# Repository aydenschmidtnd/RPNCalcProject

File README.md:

# RPNCalcProject

Due to the cost of reverse polish notation (RPN) calculators, I wanted to make the attempt at creating one myself.
I would do this all from scratch making my own PCB, creating my own code, and figuring out how to create a calculator-like case.

I want to go ahead and do this with the MSP430G2533 Microcontroller since I have a development board with me with that MCU.

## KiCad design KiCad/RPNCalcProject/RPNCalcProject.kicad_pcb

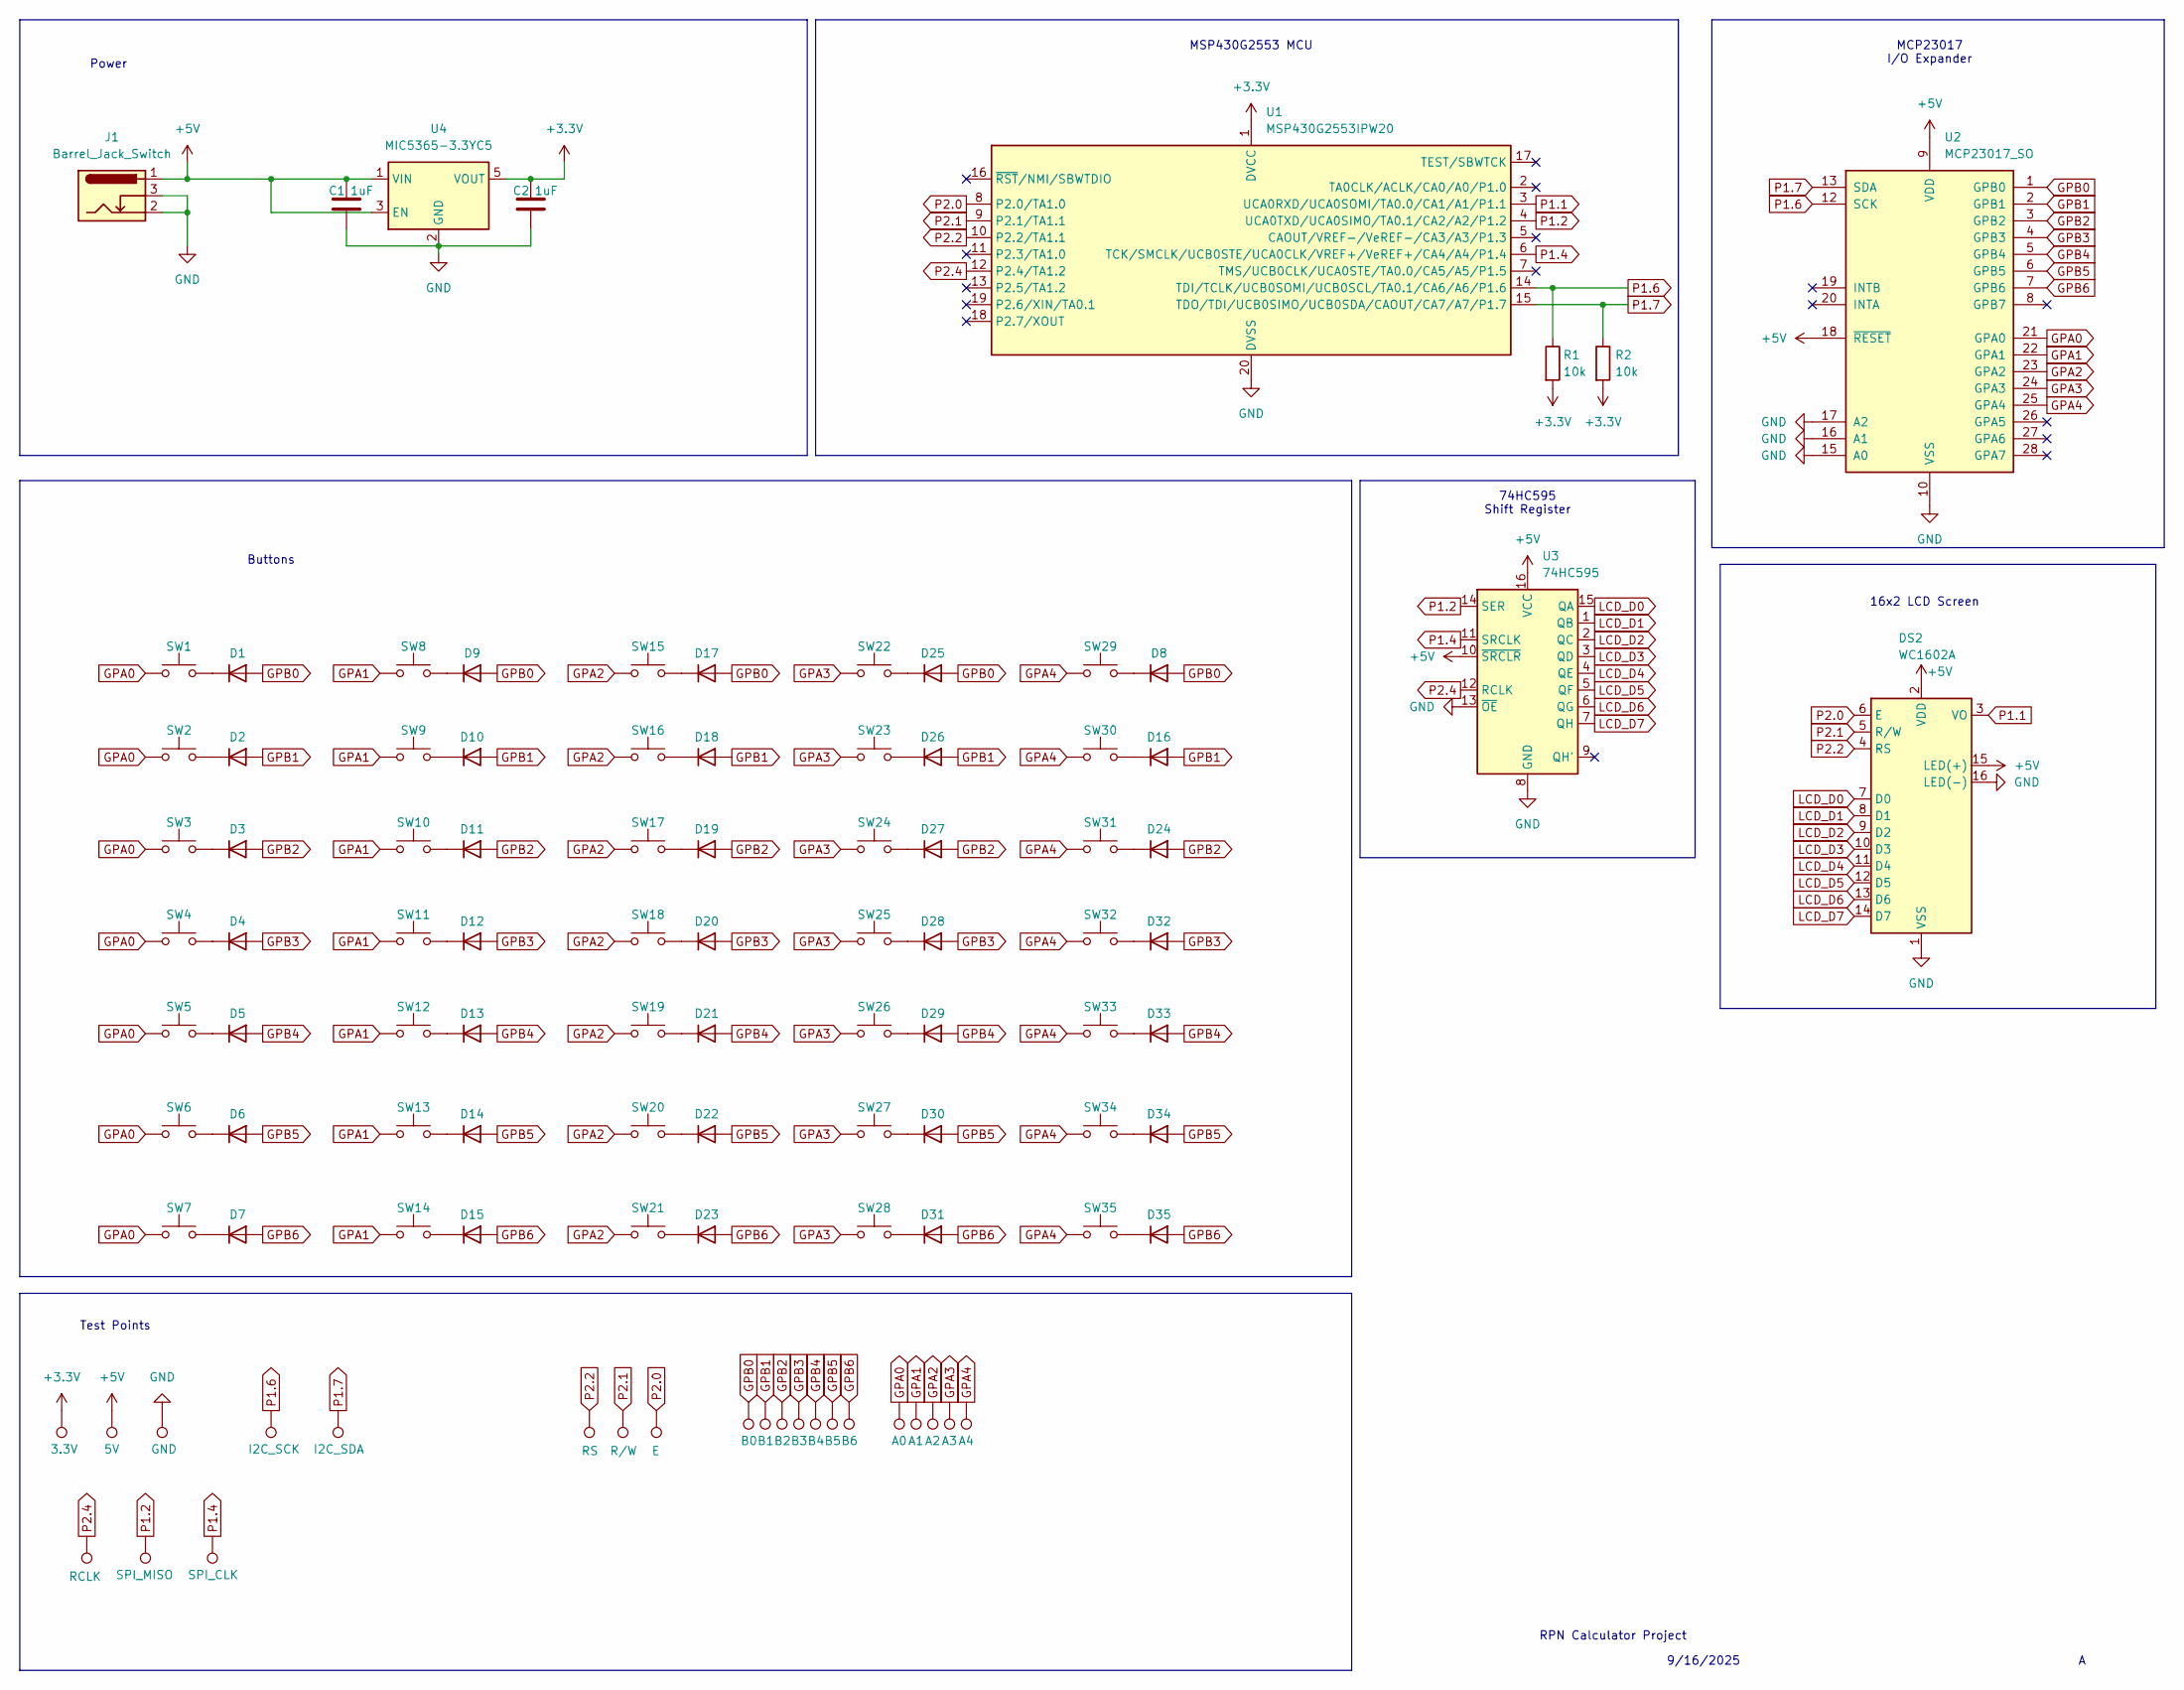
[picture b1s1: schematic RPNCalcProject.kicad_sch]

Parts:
C1, C2: 1uF; C_0201_0603Metric_Pad0.64x0.40mm_HandSolder
D1, D2, D3, D4, D5, D6, D7, D8, D9, D10, D11, D12, D13, D14, D15, D16, D17, D18, D19, D20, D21, D22, D23, D24, D25, D26, D27, D28, D29, D30, D31, D32, D33, D34, D35: 1N4148WS; D_DO-35_SOD27_P2.54mm_Vertical_KathodeUp
DS2: WC1602A
J1: Barrel_Jack_Switch; BarrelJack_CLIFF_FC681465S_SMT_Horizontal
R1, R2: 10k; R_0603_1608Metric_Pad0.98x0.95mm_HandSolder
SW1: RCL; Tactile momentary button
SW2: SIN; Tactile momentary button
SW3: ENTER; Tactile momentary button
SW4: SYMBOLS; Tactile momentary button
SW5: SWITCH; Tactile momentary button
SW6: CLEAR; Tactile momentary button
SW7: OFF/ON; Tactile momentary button
SW8: STACK_DOWN; Tactile momentary button
SW9: COS; Tactile momentary button
SW10: IMAGINARY; Tactile momentary button
SW11: NUM_7; Tactile momentary button
SW12: NUM_4; Tactile momentary button
SW13: NUM_1; Tactile momentary button
SW14: NUM_0; Tactile momentary button
SW15: SWAP; Tactile momentary button
SW16: TAN; Tactile momentary button
SW17: NEGATE; Tactile momentary button
SW18: NUM_8; Tactile momentary button
SW19: NUM_5; Tactile momentary button
SW20: NUM_2; Tactile momentary button
SW21: DECIMAL; Tactile momentary button
SW22: ARROW_LEFT; Tactile momentary button
SW23: POWER; Tactile momentary button
SW24: ENG_NOTATION; Tactile momentary button
SW25: NUM_9; Tactile momentary button
SW26: NUM_6; Tactile momentary button
SW27: NUM_3; Tactile momentary button
SW28: FACTORIAL; Tactile momentary button
SW29: ARROW_RIGHT; Tactile momentary button
SW30: INVERSE; Tactile momentary button
SW31: BACKSPACE; Tactile momentary button
SW32: DIVIDE; Tactile momentary button
SW33: MULTIPLY; Tactile momentary button
SW34: SUBTRACT; Tactile momentary button
SW35: ADD; Tactile momentary button
TP1: 3.3V; TestPoint_Pad_D1.0mm
TP2: 5V; TestPoint_Pad_D1.0mm
TP3: GND; TestPoint_THTPad_1.0x1.0mm_Drill0.5mm
TP4: I2C_SCK; TestPoint_Pad_D1.0mm
TP5: I2C_SDA; TestPoint_Pad_D1.0mm
TP6: SPI_MISO; TestPoint_Pad_D1.0mm
TP7: SPI_CLK; TestPoint_Pad_D1.0mm
TP16: RS; TestPoint_Pad_D1.0mm
TP17: R/W; TestPoint_Pad_D1.0mm
TP18: E; TestPoint_Pad_D1.0mm
TP19: RCLK; TestPoint_Pad_D1.0mm
TP20: B0; TestPoint_Pad_D1.0mm
TP21: B1; TestPoint_Pad_D1.0mm
TP22: B2; TestPoint_Pad_D1.0mm
TP23: B3; TestPoint_Pad_D1.0mm
TP24: B4; TestPoint_Pad_D1.0mm
TP25: B5; TestPoint_Pad_D1.0mm
TP26: B6; TestPoint_Pad_D1.0mm
TP27: A0; TestPoint_THTPad_D1.0mm_Drill0.5mm
TP28: A1; TestPoint_THTPad_D1.0mm_Drill0.5mm
TP29: A2; TestPoint_THTPad_D1.0mm_Drill0.5mm
TP30: A3; TestPoint_THTPad_D1.0mm_Drill0.5mm
TP31: A4; TestPoint_THTPad_D1.0mm_Drill0.5mm
U1: MSP430G2553IPW20; DIP-20_W7.62mm_Socket_LongPads
U2: MCP23017_SO; SOIC-28W_7.5x17.9mm_P1.27mm
U3: 74HC595; TSSOP-16_4.4x5mm_P0.65mm
U4: MIC5365-3.3YC5; SOT-353_SC-70-5

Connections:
+3.3V: C2.1, R1.2, R2.2, TP1.1, U1.1 (DVCC), U4.5 (VOUT)
+5V: C1.1, DS2.2 (VDD), DS2.15 (LED(+)), J1.1, TP2.1, U2.9 (VDD), U2.18 (~RESET), U3.10 (~SRCLR), U3.16 (VCC), U4.1 (VIN), U4.3 (EN)
GND: C1.2, C2.2, DS2.1 (VSS), DS2.16 (LED(-)), J1.2, J1.3, TP3.1, U1.20 (DVSS), U2.10 (VSS), U2.15 (A0), U2.16 (A1), U2.17 (A2), U3.8 (GND), U3.13 (~OE), U4.2 (GND)
GPA0: SW1.1 (A), SW1.2 (A), SW2.1 (A), SW2.2 (A), SW3.1 (A), SW3.2 (A), SW4.1 (A), SW4.2 (A), SW5.1 (A), SW5.2 (A), SW6.1 (A), SW6.2 (A), SW7.1 (A), SW7.2 (A), TP27.1, U2.21 (GPA0)
GPA1: SW8.1 (A), SW8.2 (A), SW9.1 (A), SW9.2 (A), SW10.1 (A), SW10.2 (A), SW11.1 (A), SW11.2 (A), SW12.1 (A), SW12.2 (A), SW13.1 (A), SW13.2 (A), SW14.1 (A), SW14.2 (A), TP28.1, U2.22 (GPA1)
GPA2: SW15.1 (A), SW15.2 (A), SW16.1 (A), SW16.2 (A), SW17.1 (A), SW17.2 (A), SW18.1 (A), SW18.2 (A), SW19.1 (A), SW19.2 (A), SW20.1 (A), SW20.2 (A), SW21.1 (A), SW21.2 (A), TP29.1, U2.23 (GPA2)
GPA3: SW22.1 (A), SW22.2 (A), SW23.1 (A), SW23.2 (A), SW24.1 (A), SW24.2 (A), SW25.1 (A), SW25.2 (A), SW26.1 (A), SW26.2 (A), SW27.1 (A), SW27.2 (A), SW28.1 (A), SW28.2 (A), TP30.1, U2.24 (GPA3)
GPA4: SW29.1 (A), SW29.2 (A), SW30.1 (A), SW30.2 (A), SW31.1 (A), SW31.2 (A), SW32.1 (A), SW32.2 (A), SW33.1 (A), SW33.2 (A), SW34.1 (A), SW34.2 (A), SW35.1 (A), SW35.2 (A), TP31.1, U2.25 (GPA4)
GPB0: D1.2 (A), D8.2 (A), D9.2 (A), D17.2 (A), D25.2 (A), TP20.1, U2.1 (GPB0)
GPB1: D2.2 (A), D10.2 (A), D16.2 (A), D18.2 (A), D26.2 (A), TP21.1, U2.2 (GPB1)
GPB2: D3.2 (A), D11.2 (A), D19.2 (A), D24.2 (A), D27.2 (A), TP22.1, U2.3 (GPB2)
GPB3: D4.2 (A), D12.2 (A), D20.2 (A), D28.2 (A), D32.2 (A), TP23.1, U2.4 (GPB3)
GPB4: D5.2 (A), D13.2 (A), D21.2 (A), D29.2 (A), D33.2 (A), TP24.1, U2.5 (GPB4)
GPB5: D6.2 (A), D14.2 (A), D22.2 (A), D30.2 (A), D34.2 (A), TP25.1, U2.6 (GPB5)
GPB6: D7.2 (A), D15.2 (A), D23.2 (A), D31.2 (A), D35.2 (A), TP26.1, U2.7 (GPB6)
LCD_D0: DS2.7 (D0), U3.15 (QA)
LCD_D1: DS2.8 (D1), U3.1 (QB)
LCD_D2: DS2.9 (D2), U3.2 (QC)
LCD_D3: DS2.10 (D3), U3.3 (QD)
LCD_D4: DS2.11 (D4), U3.4 (QE)
LCD_D5: DS2.12 (D5), U3.5 (QF)
LCD_D6: DS2.13 (D6), U3.6 (QG)
LCD_D7: DS2.14 (D7), U3.7 (QH)
unnamed: D1.1 (K), SW1.3 (B), SW1.4 (B)
unnamed: D2.1 (K), SW2.3 (B), SW2.4 (B)
unnamed: D3.1 (K), SW3.3 (B), SW3.4 (B)
unnamed: D4.1 (K), SW4.3 (B), SW4.4 (B)
unnamed: D5.1 (K), SW5.3 (B), SW5.4 (B)
unnamed: D6.1 (K), SW6.3 (B), SW6.4 (B)
unnamed: D7.1 (K), SW7.3 (B), SW7.4 (B)
unnamed: D8.1 (K), SW29.3 (B), SW29.4 (B)
unnamed: D9.1 (K), SW8.3 (B), SW8.4 (B)
unnamed: D10.1 (K), SW9.3 (B), SW9.4 (B)
unnamed: D11.1 (K), SW10.3 (B), SW10.4 (B)
unnamed: D12.1 (K), SW11.3 (B), SW11.4 (B)
unnamed: D13.1 (K), SW12.3 (B), SW12.4 (B)
unnamed: D14.1 (K), SW13.3 (B), SW13.4 (B)
unnamed: D15.1 (K), SW14.3 (B), SW14.4 (B)
unnamed: D16.1 (K), SW30.3 (B), SW30.4 (B)
unnamed: D17.1 (K), SW15.3 (B), SW15.4 (B)
unnamed: D18.1 (K), SW16.3 (B), SW16.4 (B)
unnamed: D19.1 (K), SW17.3 (B), SW17.4 (B)
unnamed: D20.1 (K), SW18.3 (B), SW18.4 (B)
unnamed: D21.1 (K), SW19.3 (B), SW19.4 (B)
unnamed: D22.1 (K), SW20.3 (B), SW20.4 (B)
unnamed: D23.1 (K), SW21.3 (B), SW21.4 (B)
unnamed: D24.1 (K), SW31.3 (B), SW31.4 (B)
unnamed: D25.1 (K), SW22.3 (B), SW22.4 (B)
unnamed: D26.1 (K), SW23.3 (B), SW23.4 (B)
unnamed: D27.1 (K), SW24.3 (B), SW24.4 (B)
unnamed: D28.1 (K), SW25.3 (B), SW25.4 (B)
unnamed: D29.1 (K), SW26.3 (B), SW26.4 (B)
unnamed: D30.1 (K), SW27.3 (B), SW27.4 (B)
unnamed: D31.1 (K), SW28.3 (B), SW28.4 (B)
unnamed: D32.1 (K), SW32.3 (B), SW32.4 (B)
unnamed: D33.1 (K), SW33.3 (B), SW33.4 (B)
unnamed: D34.1 (K), SW34.3 (B), SW34.4 (B)
unnamed: D35.1 (K), SW35.3 (B), SW35.4 (B)
P1.1: DS2.3 (VO), U1.3 (UCA0RXD/UCA0SOMI/TA0.0/CA1/A1/P1.1)
P1.2: TP6.1, U1.4 (UCA0TXD/UCA0SIMO/TA0.1/CA2/A2/P1.2), U3.14 (SER)
P1.4: TP7.1, U1.6 (TCK/SMCLK/UCB0STE/UCA0CLK/VREF+/VeREF+/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), U3.11 (SRCLK)
P1.6: R1.1, TP4.1, U1.14 (TDI/TCLK/UCB0SOMI/UCB0SCL/TA0.1/CA6/A6/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), U2.12 (SCK)
P1.7: R2.1, TP5.1, U1.15 (TDO/TDI/UCB0SIMO/UCB0SDA/CAOUT/CA7/A7/P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), U2.13 (SDA)
P2.0: DS2.6 (E), TP18.1, U1.8 (P2.0/TA1.0)
P2.1: DS2.5 (R/W), TP17.1, U1.9 (P2.1/TA1.1)
P2.2: DS2.4 (RS), TP16.1, U1.10 (P2.2/TA1.1)
P2.4: TP19.1, U1.12 (P2.4/TA1.2), U3.12 (RCLK)

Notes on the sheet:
74HC595 Shift Register
Buttons
MSP430G2553 MCU
9/16/2025
MCP23017 I/O Expander
16x2 LCD Screen
RPN Calculator Project
Test Points
Power

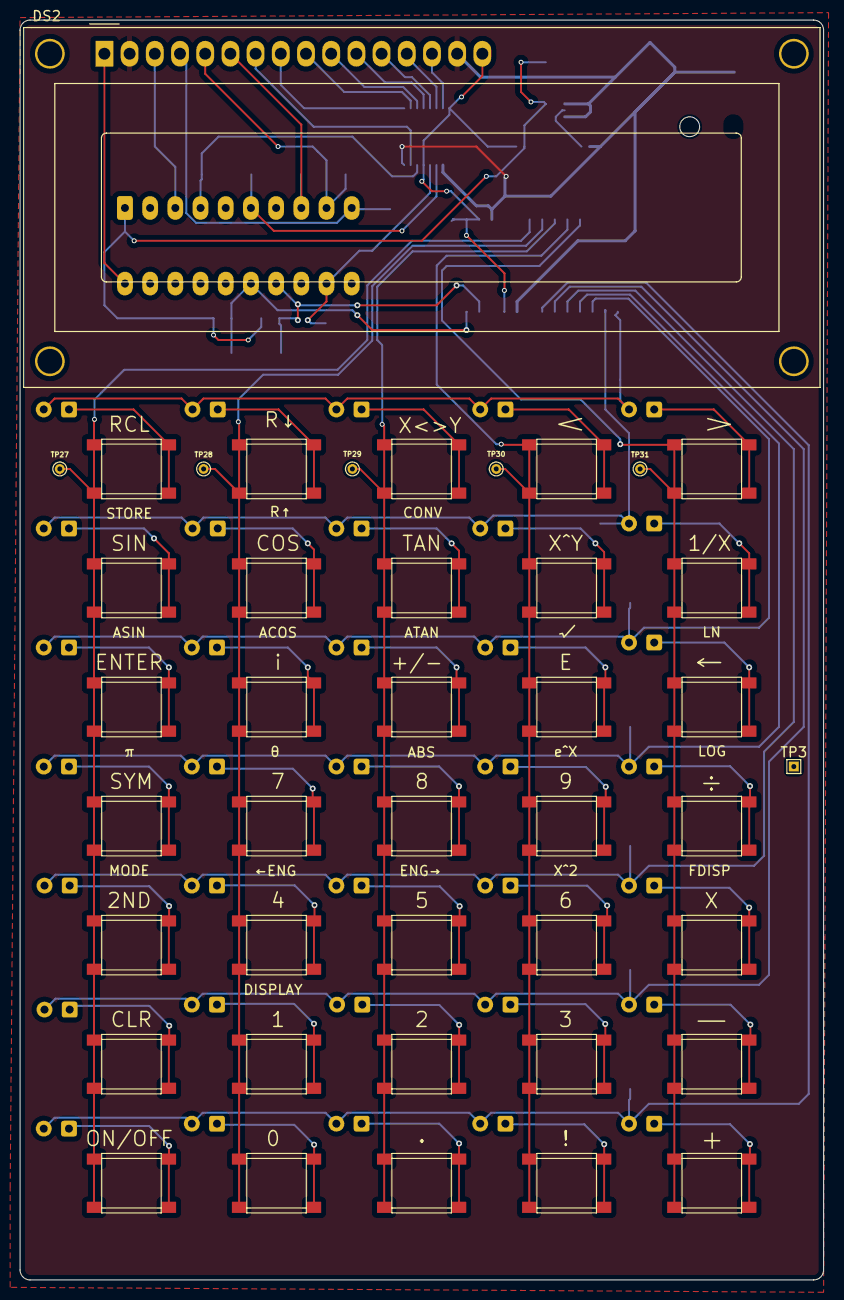
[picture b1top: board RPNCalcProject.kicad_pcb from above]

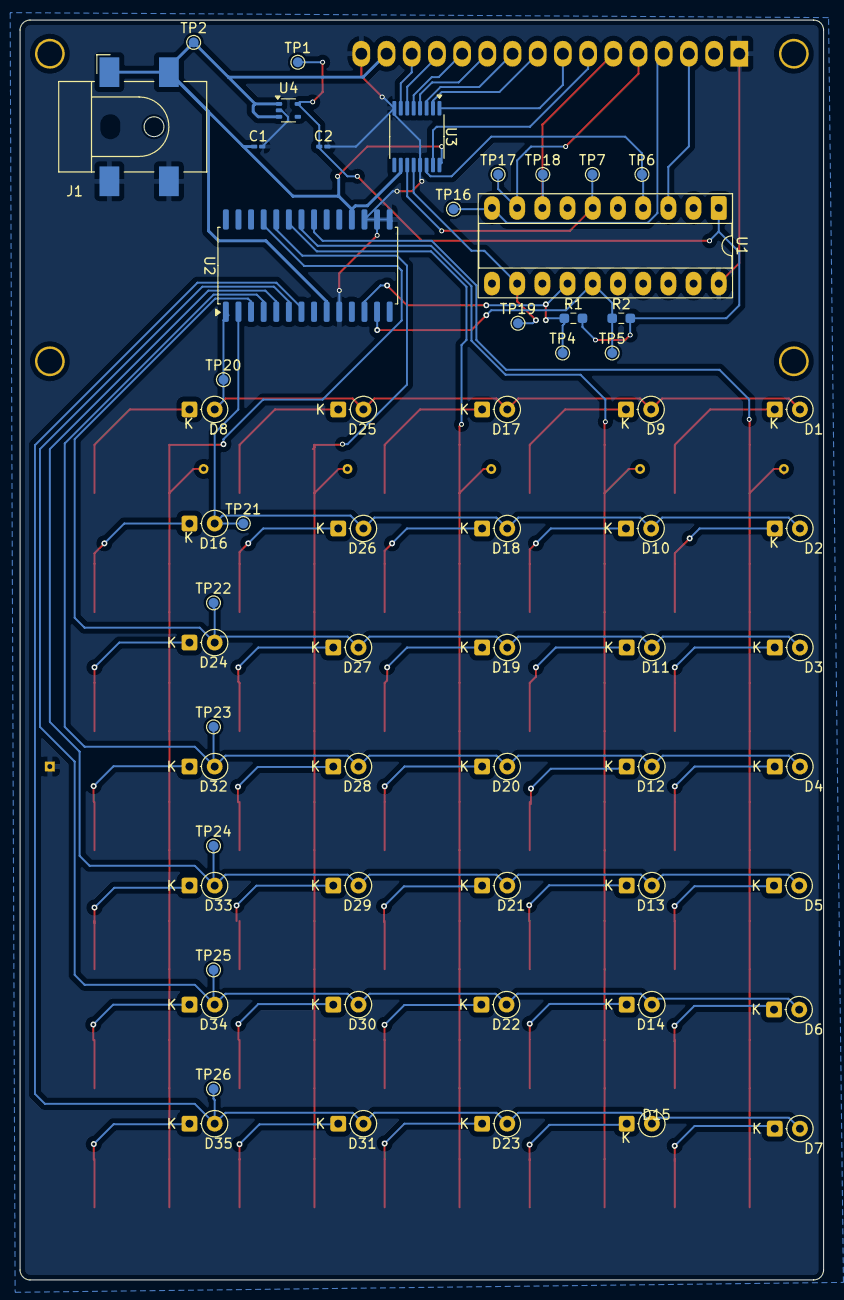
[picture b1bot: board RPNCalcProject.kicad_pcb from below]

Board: 2 copper layers, 81.0 x 127.0 mm, 103 parts (61 on the bottom side), 67 nets.

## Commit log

2025-05-10 Checkin of software/hardware diagrams + high level requirements
2025-05-16 Made initial diagram for software
2025-05-16 Made changes to High Level Requirements
2025-06-17 Initial commit of MSP430G2553 Project
2025-06-24 Added LCD functionality
2025-06-24 Added .gitignore
2025-06-25 Corrected enable as BIT7 instead of BIT8 and changed delay
2025-07-27 Initial commit of documentation.
    This includes
    1) Draft of high level requirements
    2) Pin assignments
2025-07-27 Moved main.c to src folder. Moved high level requirements to documents folder
2025-07-27 Initial commit of MAIN and SPI code.
2025-07-27 Changes to GPIODriver and LCD.
2025-08-06 Commit of Kicad Files
2025-08-06 Commit of I2C module
2025-08-06 Initial commit of timer module set for 1 ms
2025-08-06 Updated documents
2025-08-06 Changed from GPIOSetup to InitGPIO to conform with rest of code
2025-08-06 Created InitLCD function and fixed bug where if you wrote to same line it wouldn't start from beginning
2025-08-06 Small changes to SPI
    Added delay at end; Made SPI 500kHz with respect to 16 Mhz SMCLK
2025-08-06 Recent temp changes for main.c
2025-08-07 Cleaner formatting; removed redundant lines in LCD module
2025-08-07 Update to pin assignments
2025-08-08 Updated kicad schematic
2025-09-16 Updated schematic, added button layout plan
2025-09-17 Updated Kicad PCB/Schematic
    Finished schematic and almost finished routing PCB
2025-09-17 Updated pin assignment / Removed calculator buttons md
2025-11-11 Add KiCad project backups and .vscode to .gitignore
2025-11-11 Add GerberFiles directory to .gitignore
2025-11-16 Added reference pdfs
2025-12-08 Rename and Reorganize files
2025-12-08 Saving progress on Software Diagram
2025-12-08 Formatting
